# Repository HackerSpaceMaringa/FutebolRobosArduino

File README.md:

# Futebol de Robôs

O projeto Futebol de Robôs surgiu da parceria do HackerSpace Maringá com o Professor Nardênio Almeida Martins, do Departamento de Informática (DIN) da Universidade Estadual de Maringá (UEM). O projeto inclui, desenvolver os circuitos, PCB, firmware (no microcontrolador) e software (com as estratégias e visão computacional). Devido a graduação de vários membros, o projeto caminha dentro do possível. Atualmente, foram impressas as PCBs da v2, feito o firmware v1 e software de visão computacional.  

Projeto completo do Futebol de Robôs mantido pelo Hackerspace Maringá.

## Índice

- [Sobre](#sobre)
- __O Projeto__
    - [Hardware](#hardware)
        - [Microcontrolador](#microcontrolador)
        - [Comunicação](#comunicação)
        - [Controle dos Motores](#controle-dos-motores)
        - [Monitoramento da Bateria](#monitoramento-da-bateria)
    - [Software](#software)
- [Avanço do Projeto](#avanço-do-projeto)
- [Créditos](#créditos)
- [Licença](#licença)

### Sobre

TODO

### Hardware

#### Microcontrolador

O [Arduino Nano](https://www.arduino.cc/) foi escolhido como microcontrolador para este projeto por oferecer uma experiência simples e acessível, sendo fácil de utilizar para iniciantes e flexível para usuários avançados.

#### Comunicação

A comunicação foi substituída de Rádio frequência para bluetooth com o objetivo de evitar conflitos com a frequência de outros times e diminuir a complexidade do projeto. Utilizaremos um módulo HC-05 para efetuar o envio/recebimento de mensagens.

#### Controle dos Motores

Para o controle dos motores utilizaremos o circuito integrado L298. Este circuito oferece duas Pontes H no mesmo pacote, podendo receber voltagens até 46V, com correntes até 4A, além de grande imunidade à ruído nos inputs lógicos.

#### Monitoramento da Bateria

TODO

### Software

TODO

### Créditos
- [Caio Henrique Segawa Tonetti](https://github.com/LionsWrath)
- Alexandre Santiago da Silva   
- [Kariston Franzin Boveto](https://github.com/karistonf)
- [Marcos Yukio Siraichi](https://github.com/ysiraichi)
- [Christian Takashi Nakata](https://github.com/Alpaca-kun)
- Fernando Hideo Kokubu
- Willy John Nakamura Goto
- Paulo André Camargo Cocco
- [Jair Guilherme Certorio](https://github.com/jcert)

### Avanço do Projeto

O avanço do projeto pode ser acompanhado no arquivo [TODO.md](https://github.com/HackerSpaceMaringa/FutebolRobosArduino/blob/master/TODO.md)

### Licença
This project extends [GNU GPL v. 3](./LICENSE), so be aware of that, regarding copying, modifying and (re)destributing.

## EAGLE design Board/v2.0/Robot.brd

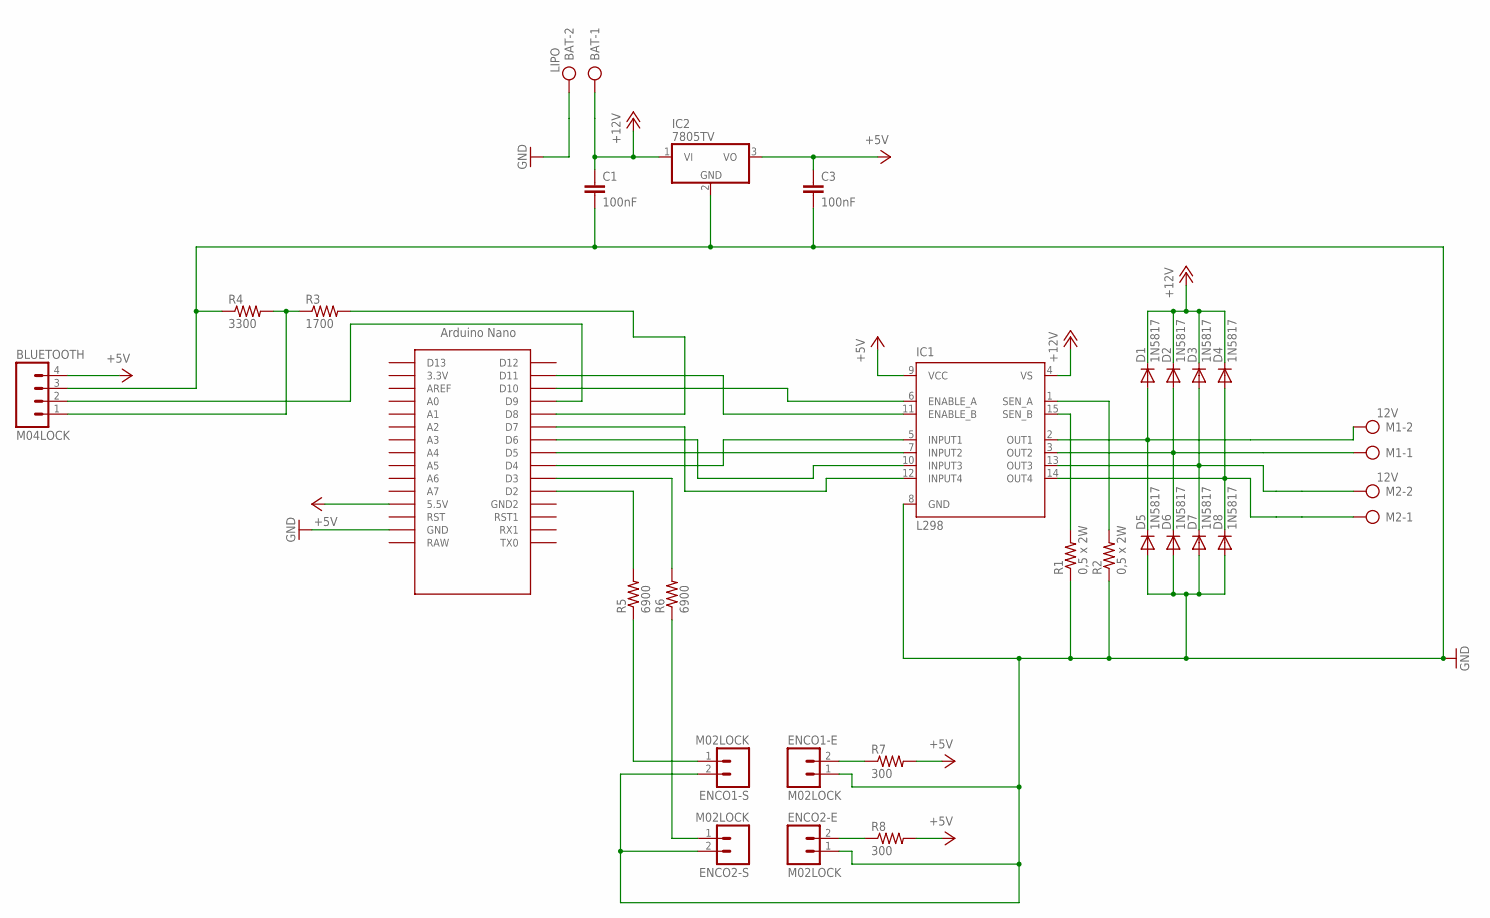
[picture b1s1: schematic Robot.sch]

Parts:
BAT: LIPO; AK500/2-H
BLUETOOTH: M04LOCK; 1X04_LOCK
C1, C3: 100nF; C050-025X075
D1, D2, D3, D4, D5, D6, D7, D8: 1N5817; DO41-10
ENCO1-E, ENCO1-S, ENCO2-E, ENCO2-S: M02LOCK; 1X02_LOCK
IC1: L298; MULTIWATT-15
IC2: 7805TV; TO220V
M1, M2: 12V; AK500/2-H
R1, R2: 0,5 x 2W; AXIAL-0.5
R3: 1700; AXIAL-0.3
R4: 3300; AXIAL-0.3
R5, R6: 6900; AXIAL-0.3
R7, R8: 300; AXIAL-0.3
U$1: NANO

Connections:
+5V: BLUETOOTH.4, C3.1, IC1.9 (VCC), IC2.3 (VO), R7.P$2 (2), R8.P$2 (2), U$1.5V (5.5V)
+12V: BAT.1, C1.1, D1.C, D2.C, D3.C, D4.C, IC1.4 (VS), IC2.1 (VI)
GND: BAT.2, BLUETOOTH.3, C1.2, C3.2, D5.A, D6.A, D7.A, D8.A, ENCO1-E.1, ENCO1-S.2, ENCO2-E.1, ENCO2-S.2, IC1.8 (GND), IC2.2 (GND), R1.P$1 (1), R2.P$1 (1), R4.P$1 (1), U$1.GND
unnamed: D1.A, D5.C, IC1.2 (OUT1), M1.2
unnamed: D3.A, D7.C, IC1.13 (OUT3), M2.2
unnamed: IC1.7 (INPUT2), U$1.D5
unnamed: D4.A, D8.C, IC1.14 (OUT4), M2.1
unnamed: R3.P$2 (2), U$1.D8
unnamed: D2.A, D6.C, IC1.3 (OUT2), M1.1
unnamed: IC1.5 (INPUT1), U$1.D4
unnamed: IC1.1 (SEN_A), R2.P$2 (2)
unnamed: IC1.15 (SEN_B), R1.P$2 (2)
unnamed: IC1.6 (ENABLE_A), U$1.D10
unnamed: BLUETOOTH.1, R3.P$1 (1), R4.P$2 (2)
unnamed: R5.P$2 (2), U$1.D2
unnamed: IC1.11 (ENABLE_B), U$1.D11
unnamed: IC1.10 (INPUT3), U$1.D6
unnamed: IC1.12 (INPUT4), U$1.D7
unnamed: BLUETOOTH.2, U$1.D9
unnamed: R6.P$2 (2), U$1.D3
unnamed: ENCO1-S.1, R5.P$1 (1)
unnamed: ENCO2-S.1, R6.P$1 (1)
unnamed: ENCO1-E.2, R7.P$1 (1)
unnamed: ENCO2-E.2, R8.P$1 (1)

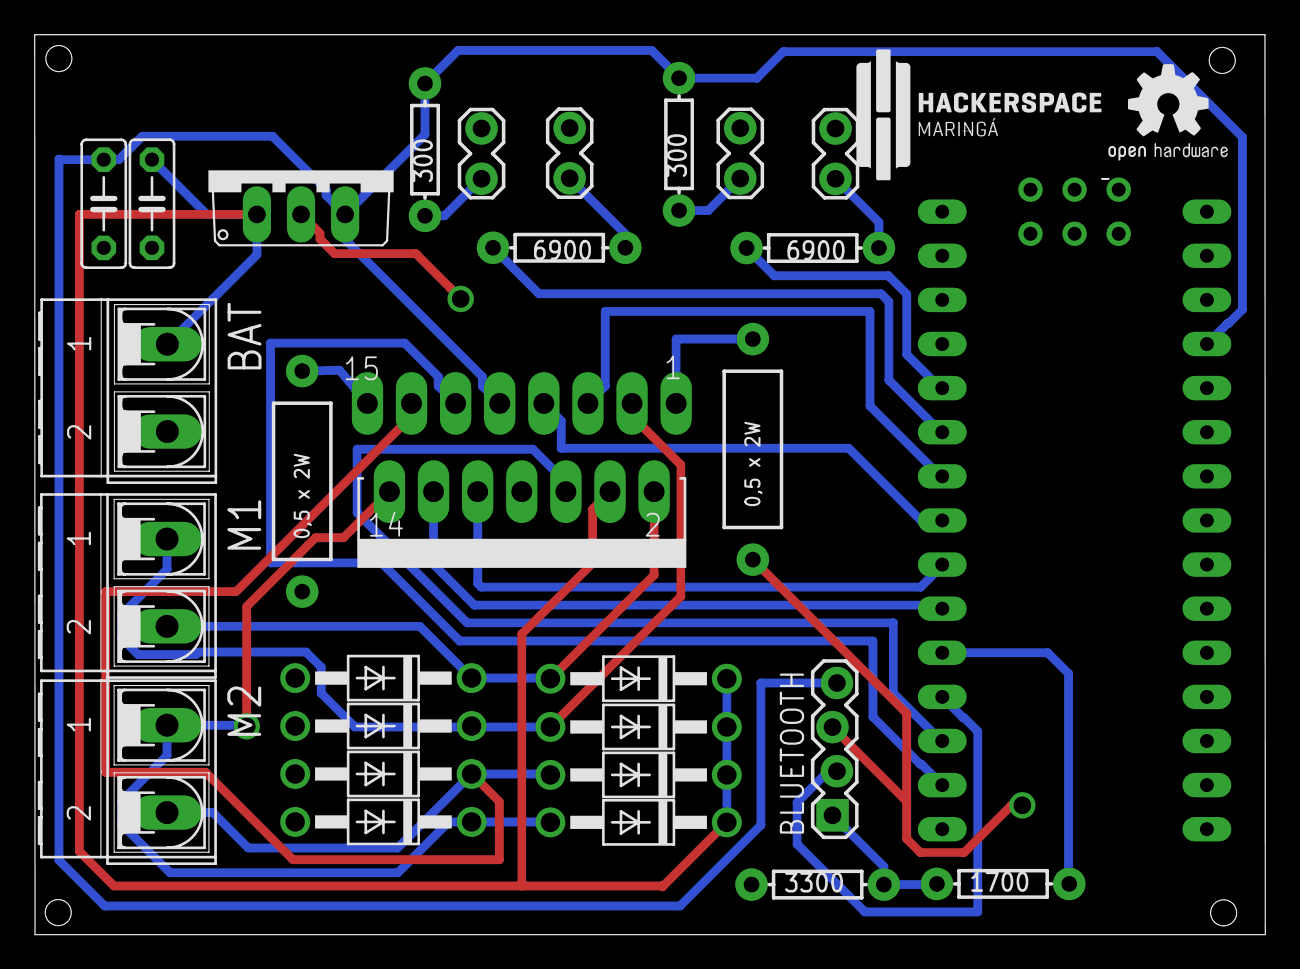
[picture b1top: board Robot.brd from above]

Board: 2 copper layers, 70.9 x 51.8 mm, 30 parts (0 on the bottom side), 24 nets.

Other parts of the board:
U$2: OSHW2

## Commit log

2016-05-04 Server side, dummy code added.
2016-05-19 Nome de funcoes do bluetooth alteradas.
2016-05-19 Codigo do motor adicionado.
2016-05-19 Codigo do servidor modificado. Deve ser executado com sudo.
2016-06-27 Codigo do motor funcionando.
2016-06-27 Codigo do bluetooth funcionando. Agora, e preciso enviar o character 0.
2016-06-27 Includes adicionados no programa principal.
2016-06-29 Funcionando no pc do caio e nome de variáveis mudadas
2016-06-29 Nome do .ino trocado
2016-07-02 FUNCIONANDO PEPEOOOOO
2016-07-05 ADD travis, LICENSE and README
2016-07-05 corrections
2016-07-05 HUEHUE
2016-07-05 CHANGED travis and README
2016-07-05 CHANGED TODO
2016-07-05 RIGHT
2016-09-26 me inclui, linkado
2016-09-26 Também quero!
2016-11-18 Add board and corrections
2016-11-18 TODO update
2017-10-04 Improve README
2017-12-11 Atualização de link de usuário do GitHub.
2018-08-01 New board version and some corrections
2018-08-07 Corrections in vias size and routing

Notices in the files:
parts and their libraries:
SparkFun-Connectors: Licensing: Creative Commons ShareAlike 4.0 International - https://creativecommons.org/licenses/by-sa/4.0
